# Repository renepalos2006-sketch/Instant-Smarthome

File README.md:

# Instant-Smarthome
An accessible plug-and-play smart home system designed for simple installation, intuitive control, and seamless home automation.

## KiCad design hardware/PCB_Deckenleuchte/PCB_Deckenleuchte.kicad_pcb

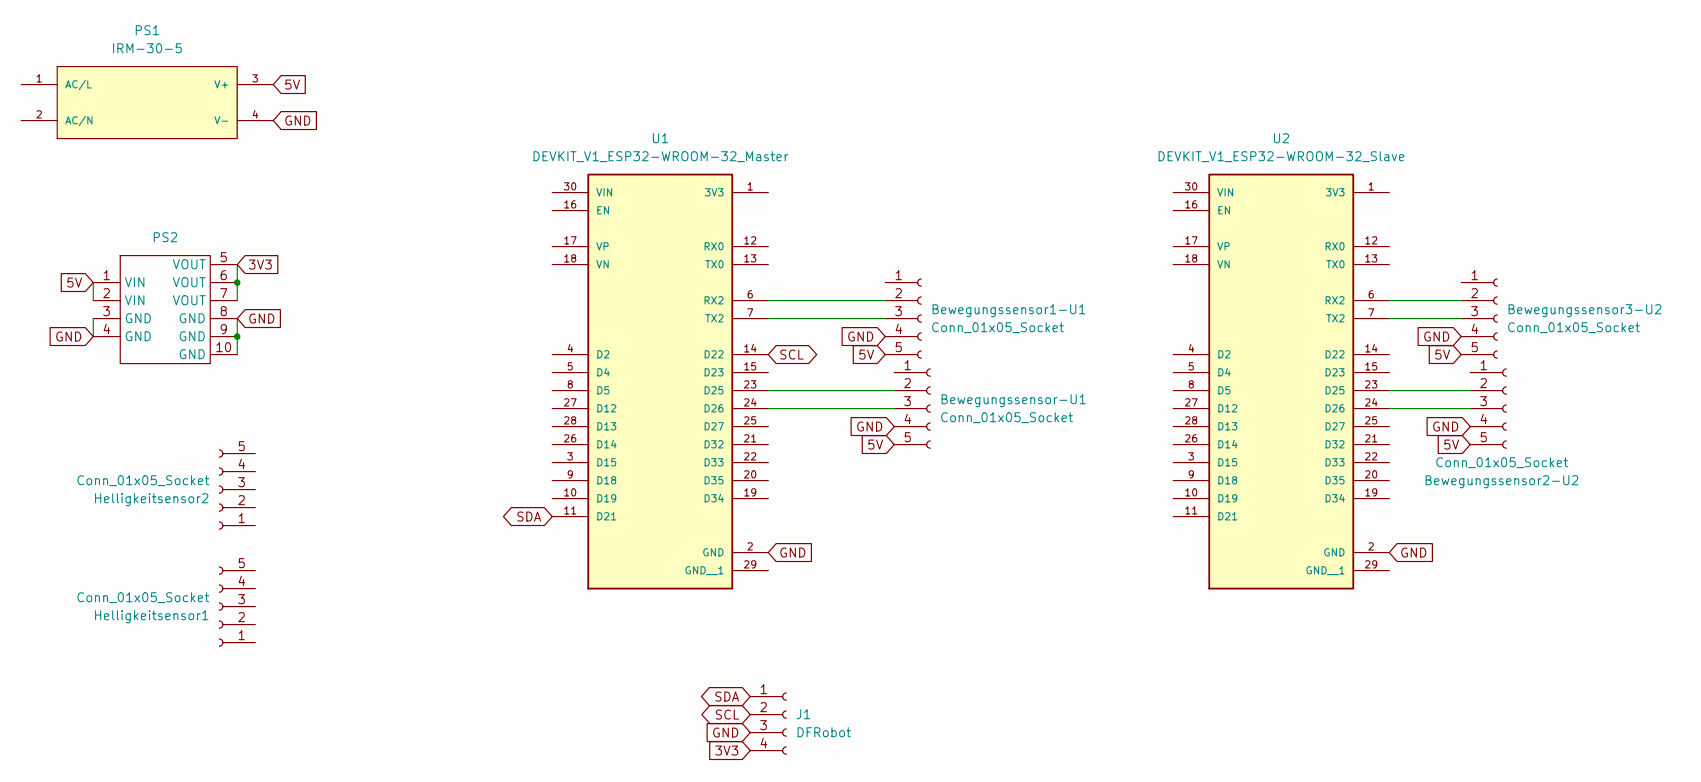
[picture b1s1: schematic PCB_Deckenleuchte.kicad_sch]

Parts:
Bewegungssensor1-U1, Bewegungssensor2-U2, Bewegungssensor3-U2: Conn_01x05_Socket; JST_XH_B5B-XH-A_1x05_P2.50mm_Vertical
Bewegungssensor-U1: Conn_01x05_Socket; JST_XH_B5B-XH-A_1x05_P2.50mm_Vertical
Helligkeitsensor1, Helligkeitsensor2: Conn_01x05_Socket; JST_XH_B5B-XH-A_1x05_P2.50mm_Vertical
J1: DFRobot; JST_PH_B4B-PH-K_1x04_P2.00mm_Vertical
PS1: IRM-30-5; CONV_IRM-30-5
PS2: DC5-36-TO-DC3V3-5
U1: DEVKIT_V1_ESP32-WROOM-32_Master; MODULE_DEVKIT_V1_ESP32-WROOM-32
U2: DEVKIT_V1_ESP32-WROOM-32_Slave; MODULE_DEVKIT_V1_ESP32-WROOM-32

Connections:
3V3: J1.4, PS2.5 (VOUT), PS2.6 (VOUT), PS2.7 (VOUT)
5V: Bewegungssensor1-U1.5, Bewegungssensor2-U2.5, Bewegungssensor3-U2.5, Bewegungssensor-U1.5, PS1.3 (V+), PS2.1 (VIN), PS2.2 (VIN)
GND: Bewegungssensor1-U1.4, Bewegungssensor2-U2.4, Bewegungssensor3-U2.4, Bewegungssensor-U1.4, J1.3, PS1.4 (V-), PS2.3 (GND), PS2.4 (GND), PS2.8 (GND), PS2.9 (GND), PS2.10 (GND), U1.2 (GND), U2.2 (GND)
unnamed: Bewegungssensor1-U1.2, U1.6 (RX2)
unnamed: Bewegungssensor1-U1.3, U1.7 (TX2)
unnamed: Bewegungssensor2-U2.2, U2.23 (D25)
unnamed: Bewegungssensor2-U2.3, U2.24 (D26)
unnamed: Bewegungssensor3-U2.2, U2.6 (RX2)
unnamed: Bewegungssensor3-U2.3, U2.7 (TX2)
unnamed: Bewegungssensor-U1.2, U1.23 (D25)
unnamed: Bewegungssensor-U1.3, U1.24 (D26)
SCL: J1.2, U1.14 (D22)
SDA: J1.1, U1.11 (D21)

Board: 2 copper layers, 11 parts (0 on the bottom side), 13 nets, no tracks yet.

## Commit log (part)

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2026-06-19 Create initial project structure
2026-06-19 Fix project structure
